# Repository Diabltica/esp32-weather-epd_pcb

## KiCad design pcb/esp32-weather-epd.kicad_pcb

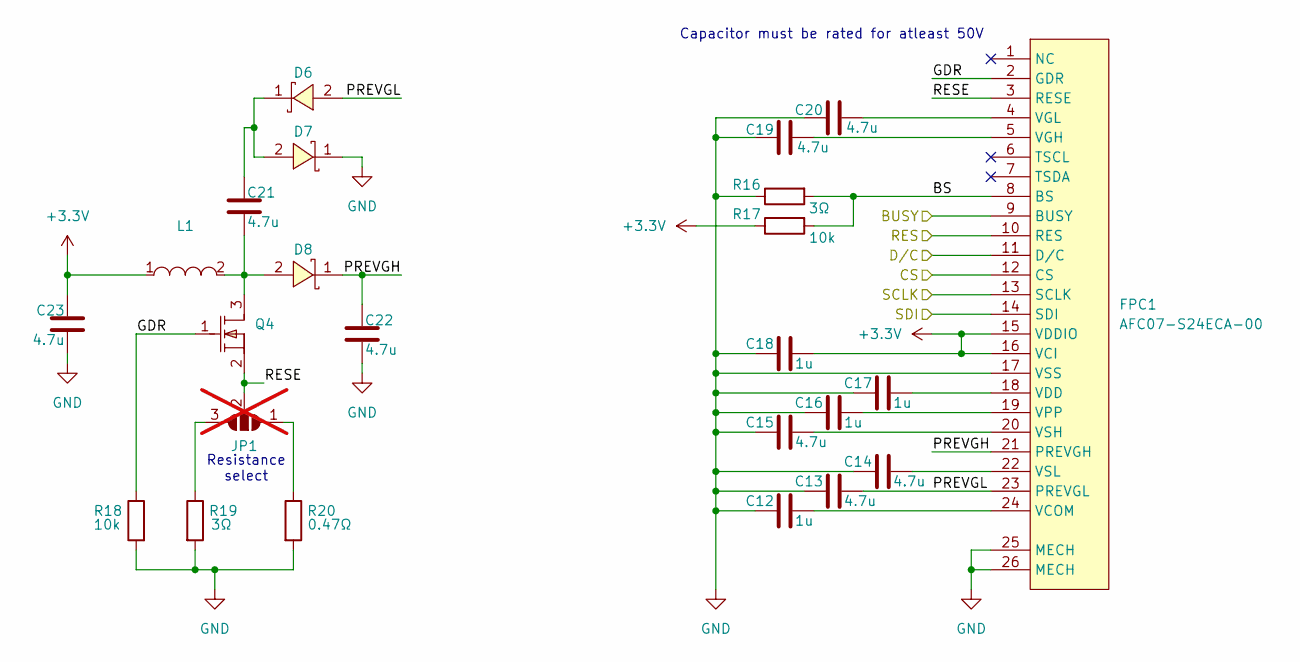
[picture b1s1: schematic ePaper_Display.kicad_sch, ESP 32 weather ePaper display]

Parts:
C12, C16, C17, C18: 1u; C_0603_1608Metric; LCSC Part C15849
C13, C14, C15, C19, C20, C21, C22, C23: 4.7u; C_0805_2012Metric; LCSC Part C98192
D6, D7, D8: MBR0530T1G; SOD-123_L2.7-W1.6-LS3.7-RD-1; LCSC Part C82046
FPC1: AFC07-S24ECA-00; FPC-SMD_AFC07-S24ECA-00; LCSC Part C262643
JP1: Resistanceselect; SolderJumper-3_P1.3mm_Open_RoundedPad1.0x1.5mm_NumberLabels; not fitted
L1: CKCSA3010-10UH/M; IND-SMD_L3.0-W3.0-1; LCSC Part C5125973
Q4: SI1308EDL-T1-GE3; SOT-323_L2.0-W1.3-P1.30-LS2.1-BR; LCSC Part C469327
R16, R19: 3Ω; R_0603_1608Metric; LCSC Part C23157
R17, R18: 10k; R_0603_1608Metric; LCSC Part C25804
R20: 0.47Ω; R_0603_1608Metric; LCSC Part C23411

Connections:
+3.3V: C18.1, C23.2, FPC1.15 (VDDIO), FPC1.16 (VCI), L1.1, R17.1; also elsewhere on the board
/BS: FPC1.8 (BS), R16.2, R17.2
/BUSY: FPC1.9 (BUSY); also elsewhere on the board
/CS: FPC1.12 (CS); also elsewhere on the board
/D/C: FPC1.11 (D/C); also elsewhere on the board
/GDR: FPC1.2 (GDR), Q4.1 (G), R18.1
/PREVGH: C22.2, D8.1 (C), FPC1.21 (PREVGH)
/PREVGL: C13.1, D6.2 (A), FPC1.23 (PREVGL)
/RES: FPC1.10 (RES); also elsewhere on the board
/RESE: FPC1.3 (RESE), JP1.2 (C), Q4.2 (S)
/SCLK: FPC1.13 (SCLK); also elsewhere on the board
/SDI: FPC1.14 (SDI); also elsewhere on the board
/VCOM: C12.1, FPC1.24 (VCOM)
GND: C12.2, C13.2, C14.2, C15.2, C16.2, C17.2, C18.2, C19.2, C20.2, C22.1, C23.1, D7.1 (C), FPC1.17 (VSS), FPC1.25 (MECH), FPC1.26 (MECH), R16.1, R18.2, R19.2, R20.2; also elsewhere on the board
unnamed: C21.2, D6.1 (C), D7.2 (A)
unnamed: C21.1, D8.2 (A), L1.2, Q4.3 (D)
unnamed: C17.1, FPC1.18 (VDD)
unnamed: C19.1, FPC1.5 (VGH)
unnamed: C20.1, FPC1.4 (VGL)
unnamed: C16.1, FPC1.19 (VPP)
unnamed: C15.1, FPC1.20 (VSH)
unnamed: C14.1, FPC1.22 (VSL)
unnamed: JP1.1 (A), R20.1
unnamed: JP1.3 (B), R19.1

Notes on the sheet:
Capacitor must be rated for atleast 50V
Resistance select

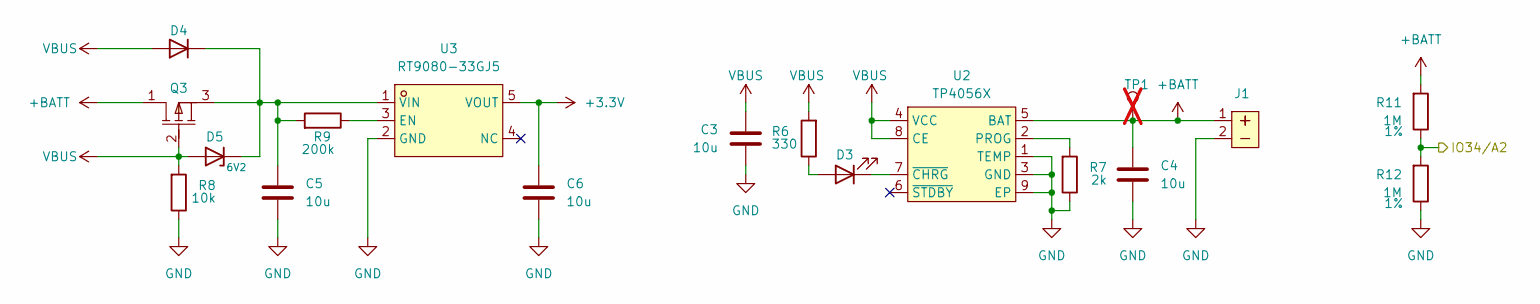
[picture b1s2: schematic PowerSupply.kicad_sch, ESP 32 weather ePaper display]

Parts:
C3, C4, C5, C6: 10u; C_0603_1608Metric; LCSC Part C96446
D3: C397045; LED_0402_1005Metric; LCSC Part C397045
D4: 1N5819; D_SOD-123F; LCSC Part C169540
D5: LM3Z6V2T1G; D_SOD-323; Zener Voltage 6V2; LCSC C131806
J1: S2B-PH-K-S(LF)(SN); CONN-TH_S2B-PH-K-S-LF-SN; LCSC Part C173752
Q3: BRCS150P02ZJ; DFN-6L_L2.0-W2.0-P0.65-BL_BRCS300PXX; LCSC Part C22448985
R6: 330; R_0603_1608Metric; LCSC Part C23138
R7: 2k; R_0603_1608Metric; LCSC Part C22975
R8: 10k; R_0603_1608Metric; LCSC Part C25804
R9: 200k; R_0603_1608Metric; LCSC Part C25811
R11, R12: 1M; R_0603_1608Metric; LCSC Part C25803
TP1: TestPoint; TestPoint_Pad_D1.0mm; not fitted
U2: TP4056X; SOP-8_L4.9-W3.9-P1.27-LS6.0-TL-EP; LCSC Part C2763448
U3: RT9080-33GJ5; SOT-23-5_L3.0-W1.5-P0.95-LS2.8-BL; LCSC Part C20617299

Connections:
+3.3V: C6.2, U3.5 (VOUT); also elsewhere on the board
+BATT: C4.2, J1.1, Q3.1 (D), R11.2, TP1.1, U2.5 (BAT)
/IO34/A2: R11.1, R12.2; also elsewhere on the board
GND: C3.1, C4.1, C5.1, C6.1, J1.2, R7.1, R8.1, R12.1, U2.1 (TEMP), U2.3 (GND), U2.9 (EP), U3.2 (GND); also elsewhere on the board
unnamed: D3.2 (A), R6.1
unnamed: D3.1 (K), U2.7 (~CHRG)
unnamed: C5.2, D4.1 (K), D5.1 (K), Q3.3 (S), R9.2, U3.1 (VIN)
unnamed: R7.2, U2.2 (PROG)
unnamed: R9.1, U3.3 (EN)
VBUS: C3.2, D4.2 (A), D5.2 (A), Q3.2 (G), R6.2, R8.2, U2.4 (VCC), U2.8 (CE); also elsewhere on the board

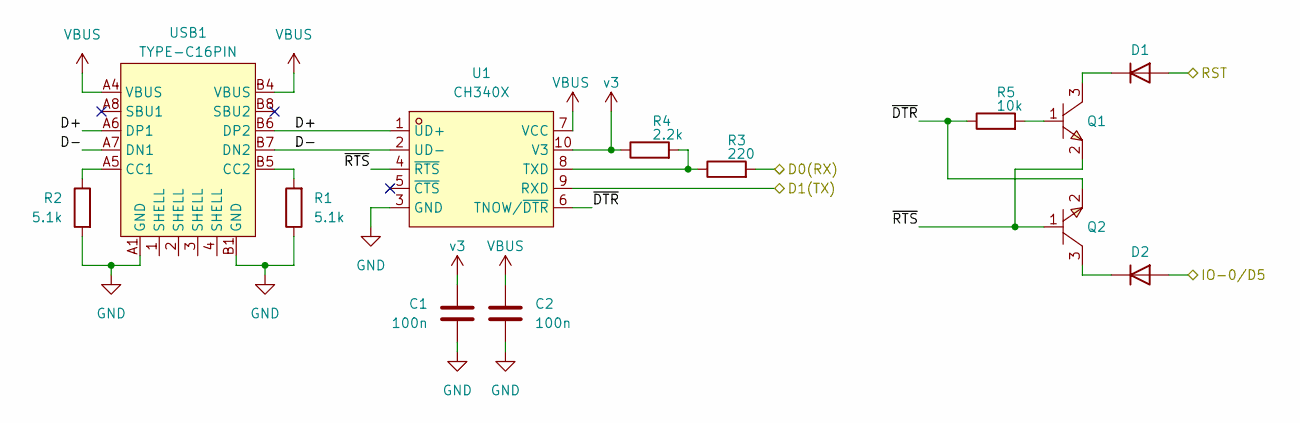
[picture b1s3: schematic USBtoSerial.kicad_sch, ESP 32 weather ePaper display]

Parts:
C1, C2: 100n; C_0603_1608Metric; LCSC Part C14663
D1, D2: 1N4148; D_SOD-323; LCSC Part C2128
Q1, Q2: S8050; SOT-23-3_L2.9-W1.6-P1.90-LS2.8-BR; LCSC Part C181158
R1, R2: 5.1k; R_0603_1608Metric; LCSC Part C23186
R3: 220; R_0603_1608Metric; LCSC Part C22962
R4: 2.2k; R_0603_1608Metric; LCSC Part C4190
R5: 10k; R_0603_1608Metric; LCSC Part C25804
U1: CH340X; MSOP-10_L3.0-W3.0-P0.50-LS5.0-BL; LCSC Part C3035748
USB1: TYPE-C16PIN; USB-C-SMD_TYPE-C16PIN; LCSC Part C393939

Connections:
/D0(RX): R3.2; also elsewhere on the board
/D1(TX): U1.9 (RXD); also elsewhere on the board
/D+: U1.1 (UD+), USB1.A6 (DP1), USB1.B6 (DP2)
/D-: U1.2 (UD-), USB1.A7 (DN1), USB1.B7 (DN2)
/IO-0/D5: D2.2 (A); also elsewhere on the board
/RST: D1.2 (A); also elsewhere on the board
/~DTR: Q2.2, R5.1, U1.6 (TNOW/~DTR)
/~RTS: Q1.2, Q2.1, U1.4 (~RTS)
GND: C1.2, C2.2, R1.1, R2.2, U1.3 (GND), USB1.A1 (GND), USB1.B1 (GND); also elsewhere on the board
unnamed: D1.1 (K), Q1.3
unnamed: D2.1 (K), Q2.3
unnamed: Q1.1, R5.2
unnamed: R3.1, R4.2, U1.8 (TXD)
unnamed: R2.1, USB1.A5 (CC1)
unnamed: R1.2, USB1.B5 (CC2)
VBUS: C2.1, U1.7 (VCC), USB1.A4 (VBUS), USB1.B4 (VBUS); also elsewhere on the board
v3: C1.1, R4.1, U1.10 (V3)

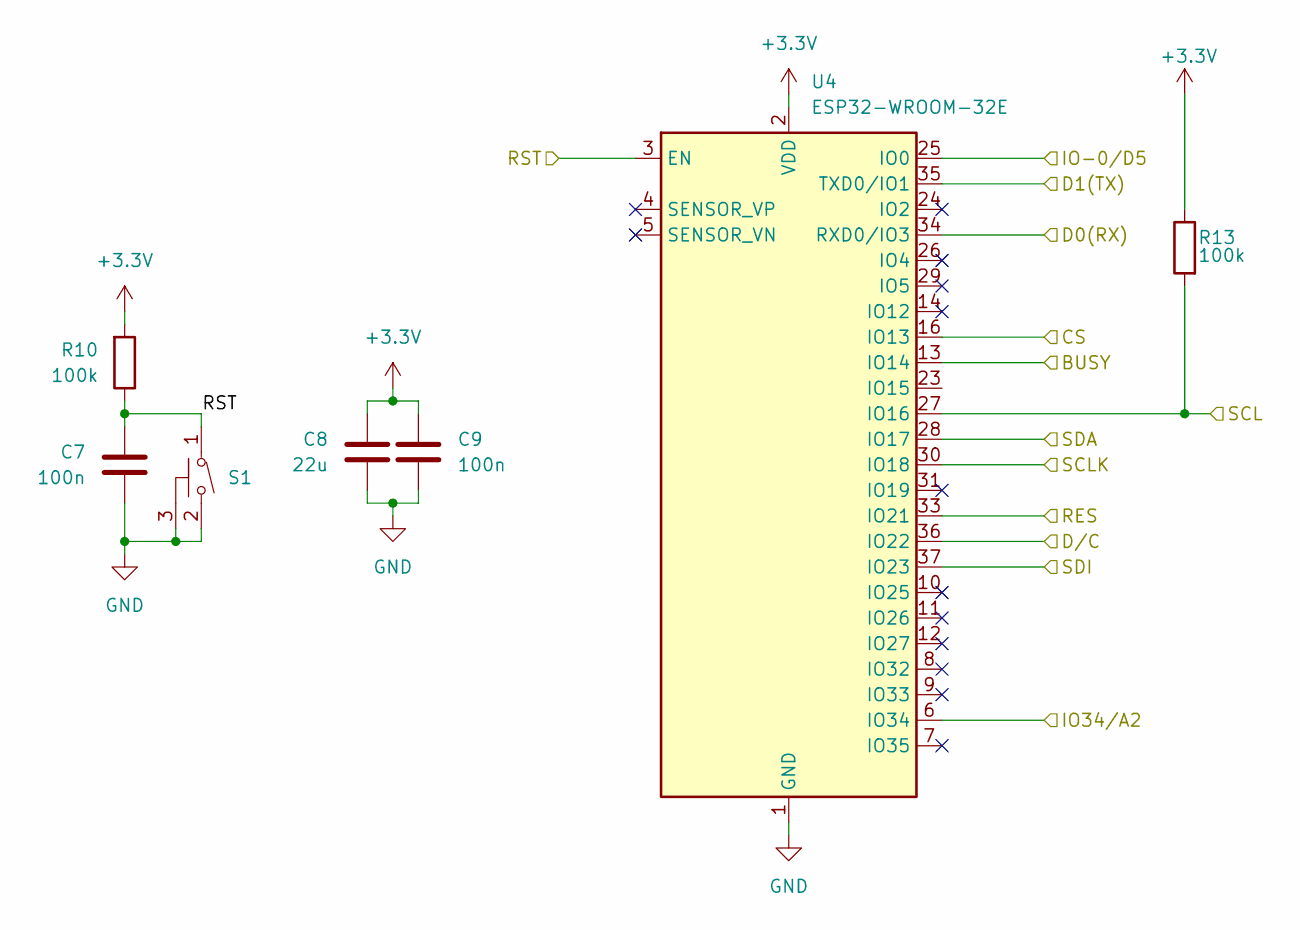
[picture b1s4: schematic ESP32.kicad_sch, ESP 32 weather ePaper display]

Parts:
C7, C9: 100n; C_0603_1608Metric; LCSC Part C14663
C8: 22u; C_0603_1608Metric; LCSC Part C59461
R10, R13: 100k; R_0603_1608Metric; LCSC Part C25803
S1: YTS1C0033BBG01; SW-SMD_YIYUAN_YTS1C003XXX; LCSC Part C5188566
U4: ESP32-WROOM-32E; ESP32-WROOM-32D; LCSC Part C701341

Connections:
+3.3V: C8.2, C9.2, R10.2, R13.1, U4.2 (VDD); also elsewhere on the board
/BUSY: U4.13 (IO14); also elsewhere on the board
/CS: U4.16 (IO13); also elsewhere on the board
/D0(RX): U4.34 (RXD0/IO3); also elsewhere on the board
/D1(TX): U4.35 (TXD0/IO1); also elsewhere on the board
/D/C: U4.36 (IO22); also elsewhere on the board
/IO34/A2: U4.6 (IO34); also elsewhere on the board
/IO-0/D5: U4.25 (IO0); also elsewhere on the board
/RES: U4.33 (IO21); also elsewhere on the board
/RST: C7.1, R10.1, S1.1, U4.3 (EN); also elsewhere on the board
/SCL: R13.2, U4.27 (IO16); also elsewhere on the board
/SCLK: U4.30 (IO18); also elsewhere on the board
/SDA: U4.28 (IO17); also elsewhere on the board
/SDI: U4.37 (IO23); also elsewhere on the board
GND: C7.2, C8.1, C9.1, S1.2, S1.3 (4), U4.1 (GND), U4.15 (GND), U4.38 (GND), U4.39 (GND); also elsewhere on the board

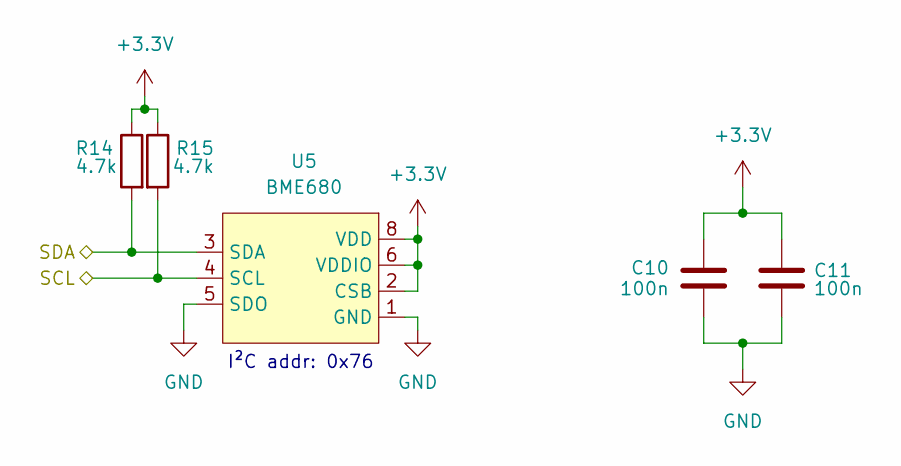
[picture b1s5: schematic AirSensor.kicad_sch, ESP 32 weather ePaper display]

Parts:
C10, C11: 100n; C_0603_1608Metric; LCSC Part C14663
R14, R15: 4.7k; R_0603_1608Metric; LCSC Part C23162
U5: BME680; LGA-8_L3.0-W3.0-P0.80-TR; LCSC Part C125972

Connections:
+3.3V: C10.2, C11.2, R14.1, R15.1, U5.2 (CSB), U5.6 (VDDIO), U5.8 (VDD); also elsewhere on the board
/SCL: R15.2, U5.4 (SCL); also elsewhere on the board
/SDA: R14.2, U5.3 (SDA); also elsewhere on the board
GND: C10.1, C11.1, U5.1 (GND), U5.5 (SDO); also elsewhere on the board

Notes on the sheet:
I²C addr: 0x76

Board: 2 copper layers, 67 parts (1 on the bottom side), 49 nets, no tracks yet.

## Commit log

2025-02-26 create kicad project file
2025-02-27 add gitignore for kicad project
2025-02-27 draw usb and power related schematic
2025-02-27 add esp32 and peripheral circuit
2025-02-28 add gas, pressure, temperature and humity sensor
2025-02-28 fix some lib link
2025-02-28 add epaper connector and needed circuitry
2025-03-01 add missing footprint and LCSC part number
2025-03-01 fix footprint
2025-03-01 add component to the pcb
2025-03-01 add missing rx and tx connection
2025-03-01 add missing i0 connection
2025-03-02 rework schematic and first draft component placement
2025-03-03 switch epaper capacitor to 0402
